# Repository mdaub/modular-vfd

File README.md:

# modular-vfd
A design for a modular vacuum fluorescent display using IV-11 VFD tubes

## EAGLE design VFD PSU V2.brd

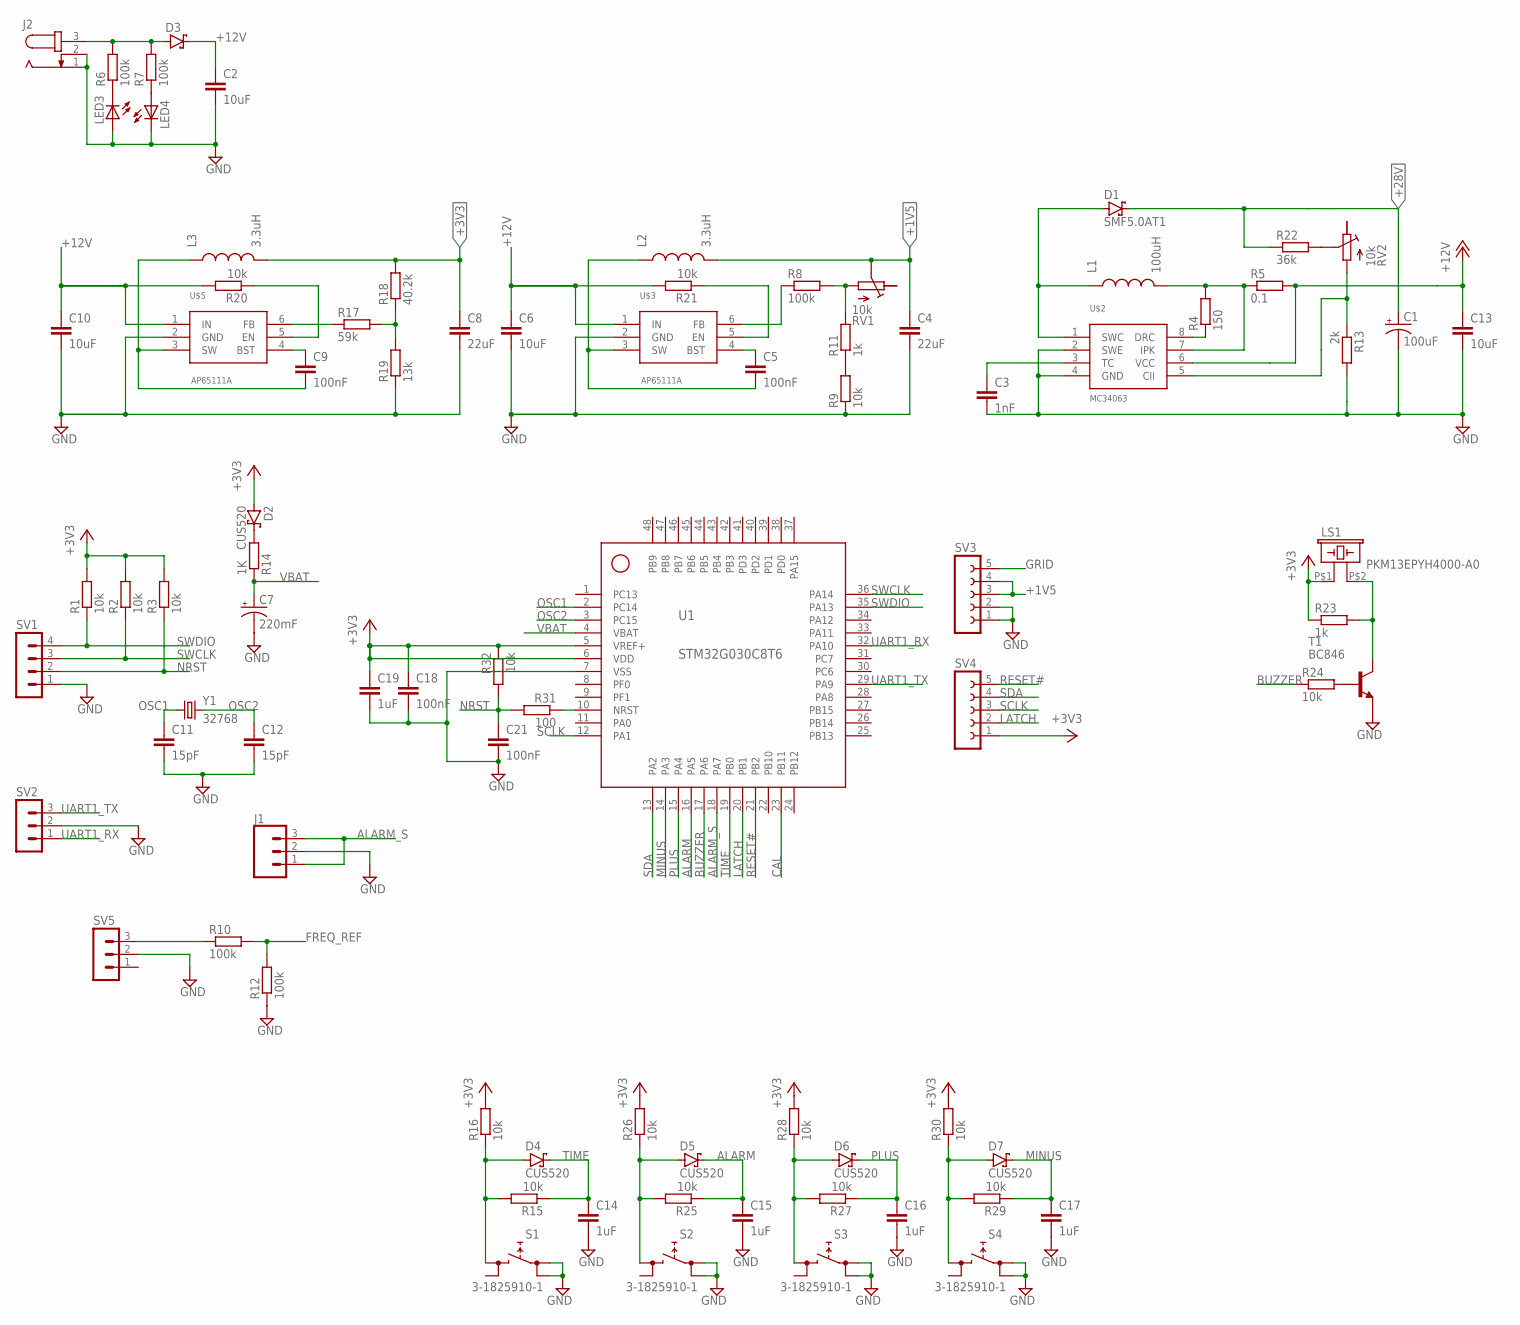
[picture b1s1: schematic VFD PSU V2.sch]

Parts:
C1: 100uF; PANASONIC_C
C2, C6, C10, C13: 10uF; C0805
C3: 1nF; C0603
C4, C8: 22uF; C0805
C5, C9, C18, C21: 100nF; C0603
C7: 220mF; 4.8-COINCELL-SCAP
C11, C12: 15pF; C0402
C14, C15, C16, C17, C19: 1uF; C0603
D1: SMF5.0AT1; SOD123FL
D2, D4, D5, D6, D7: CUS520; SOD323_ST
D3: SCHOTTKY-DIODESMD; SMB
J1: CONN_03JST-PTH-NS; JST-3-PTH-NS
J2: JACK-PLUG0; SPC4077
L1: 100uH; 2-SMD
L2, L3: 3.3uH; 1008
LED3, LED4: LEDSMT1206; 1206
LS1: PKM13EPYH4000-A0
R1, R2, R3, R9, R15, R16, R20, R21, R24, R25, R26, R27, R28, R29, R30, R32: 10k; R0603
R4: 150; R0603
R5: 0.1; R0805
R6, R7, R8, R10, R12: 100k; R0603
R11, R23: 1k; R0603
R13: 2k; R0603
R14: 1K; R0603
R17: 59k; R0603
R18: 40.2k; R0603
R19: 13k; R0603
R22: 36k; R0603
R31: 100; R0603
RV1, RV2: 10k; TC33X-2
S1, S2, S3, S4: 3-1825910-1; PANASONISWITCH
SV1: MA04-1
SV2, SV5: MA03-1
SV3, SV4: FE05W
T1: BC846; SOT23
U1: STM32G030C8T6; LQFP48
U$2: MC34063; SO08
U$3, U$5: AP65111A; TSOT23-6
Y1: 32768; 2-SMD-NO-LEAD-Q

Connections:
+1V5: C4.1, L2.P$2 (2), RV1.P$2 (S), SV3.3, SV3.4
+3V3: C8.1, C18.1, C19.1, D2.A, L3.P$2 (2), LS1.P$1 (1), R1.2, R2.2, R3.2, R16.2, R18.2, R23.1, R26.2, R28.2, R30.2, R32.1, SV4.1, U1.5 (VREF+), U1.6 (VDD)
+12V: C2.1, C6.1, C10.1, C13.1, D3.C, R5.2, R20.2, R21.2, U$2.6 (VCC), U$3.1 (IN), U$5.1 (IN)
+28V: C1.+, D1.C, R22.1
ALARM: C15.1, D5.C, R25.1, U1.16 (PA5)
ALARM_S: J1.1, J1.3, U1.18 (PA7)
BUZZER: R24.1, U1.17 (PA6)
CAL: U1.23 (PB11)
FREQ_REF: R10.2, R12.2
GND: C1.-, C2.2, C3.2, C4.2, C6.2, C7.P$2 (-), C8.2, C10.2, C11.2, C12.2, C13.2, C14.2, C15.2, C16.2, C17.2, C18.2, C19.2, C21.2, J1.2, J2.1, J2.2, LED3.A, LED4.C, R9.1, R12.1, R13.2, R19.1, S1.P$1 (0), S1.P$2 (0), S2.P$1 (0), S2.P$2 (0), S3.P$1 (0), S3.P$2 (0), S4.P$1 (0), S4.P$2 (0), SV1.1, SV2.2, SV3.1, SV3.2, SV5.2, T1.2 (E), U1.7 (VSS), U$2.2 (SWE), U$2.4 (GND), U$3.2 (GND), U$5.2 (GND)
GRID: SV3.5
LATCH: SV4.2, U1.20 (PB1)
MINUS: C17.1, D7.C, R29.1, U1.14 (PA3)
unnamed: LED3.C, R6.1
unnamed: LED4.A, R7.1
unnamed: R9.2, R11.1
unnamed: R8.1, U$3.6 (FB)
unnamed: L1.P$2 (2), R4.2, R5.1, U$2.7 (IPK)
unnamed: D3.A, J2.3, R6.2, R7.2
unnamed: R4.1, U$2.8 (DRC)
unnamed: R21.1, U$3.5 (EN)
unnamed: C5.2, L2.P$1 (1), U$3.3 (SW)
unnamed: C5.1, U$3.4 (BST)
unnamed: R8.2, R11.2, RV1.P$1 (E)
unnamed: D1.A, L1.P$1 (1), U$2.1 (SWC)
unnamed: R22.2, RV2.P$2 (S)
unnamed: C3.1, U$2.3 (TC)
unnamed: R10.1, SV5.3
unnamed: R20.1, U$5.5 (EN)
unnamed: C9.2, L3.P$1 (1), U$5.3 (SW)
unnamed: C9.1, U$5.4 (BST)
unnamed: D4.A, R15.2, R16.1, S1.P$3 (1)
unnamed: R17.1, U$5.6 (FB)
unnamed: R17.2, R18.1, R19.2
unnamed: R13.1, RV2.P$1 (E), U$2.5 (CII)
unnamed: D2.C, R14.2
unnamed: LS1.P$2 (2), R23.2, T1.3 (C)
unnamed: R24.2, T1.1 (B)
unnamed: D5.A, R25.2, R26.1, S2.P$3 (1)
unnamed: R31.1, U1.10 (NRST)
unnamed: D6.A, R27.2, R28.1, S3.P$3 (1)
unnamed: D7.A, R29.2, R30.1, S4.P$3 (1)
NRST: C21.1, R3.1, R31.2, R32.2, SV1.2
OSC1: C11.1, U1.2 (PC14), Y1.P$1 (1)
OSC2: C12.1, U1.3 (PC15), Y1.P$2 (2)
PLUS: C16.1, D6.C, R27.1, U1.15 (PA4)
RESET#: SV4.5, U1.21 (PB2)
SCLK: SV4.3, U1.12 (PA1)
SDA: SV4.4, U1.13 (PA2)
SWCLK: R2.1, SV1.3, U1.36 (PA14)
SWDIO: R1.1, SV1.4, U1.35 (PA13)
TIME: C14.1, D4.C, R15.1, U1.19 (PB0)
UART1_RX: SV2.1, U1.32 (PA10)
UART1_TX: SV2.3, U1.29 (PA9)
VBAT: C7.P$1 (+), R14.1, U1.4 (VBAT)

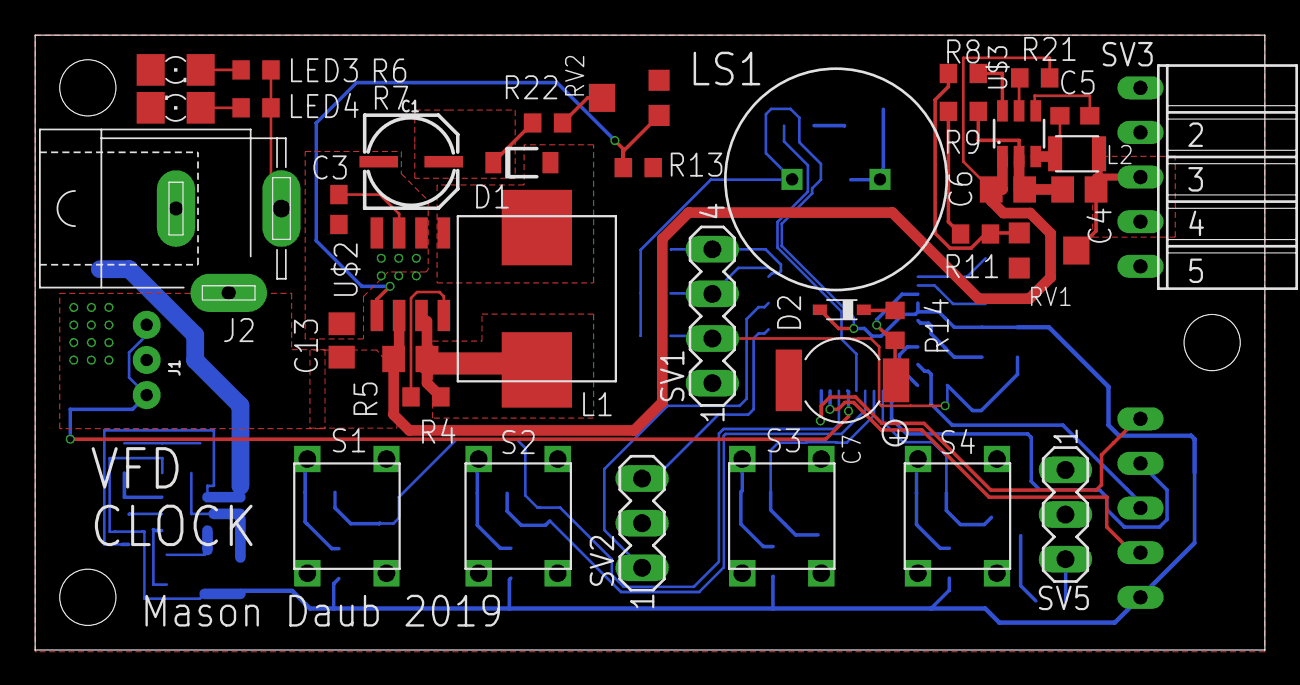
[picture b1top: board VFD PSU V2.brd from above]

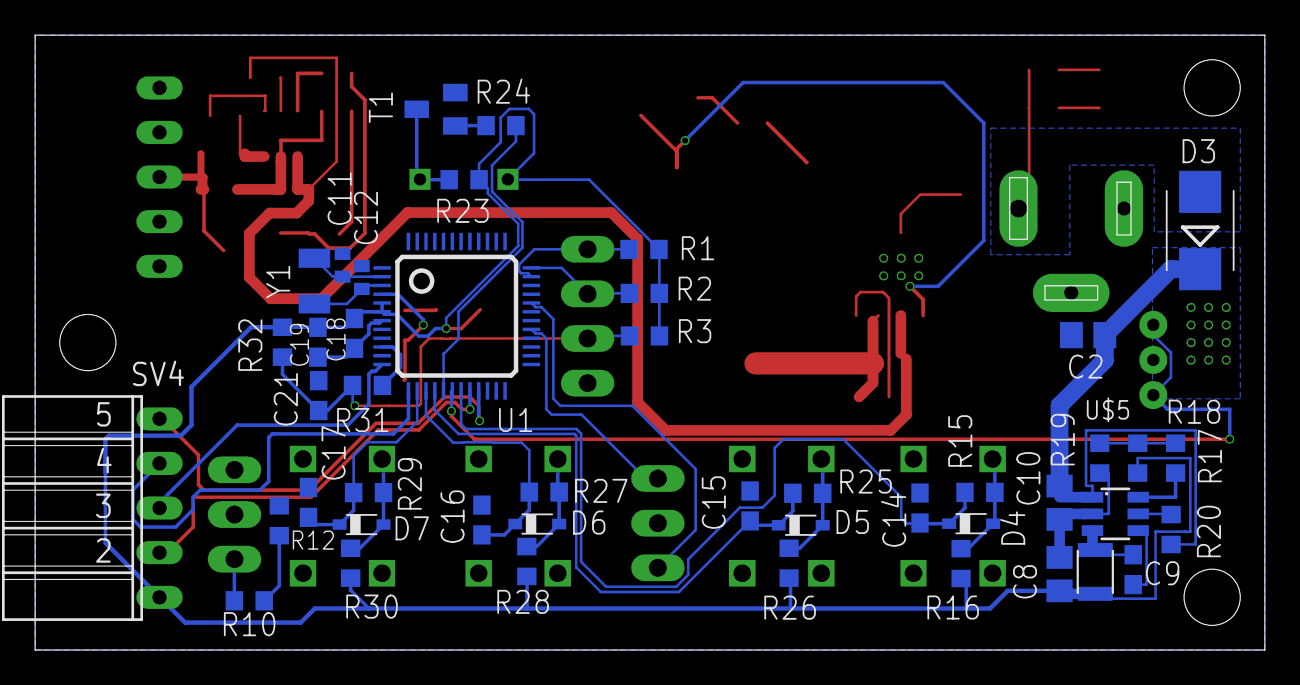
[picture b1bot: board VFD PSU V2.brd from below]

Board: 2 copper layers, 70.0 x 35.0 mm, 84 parts (45 on the bottom side), 53 nets.

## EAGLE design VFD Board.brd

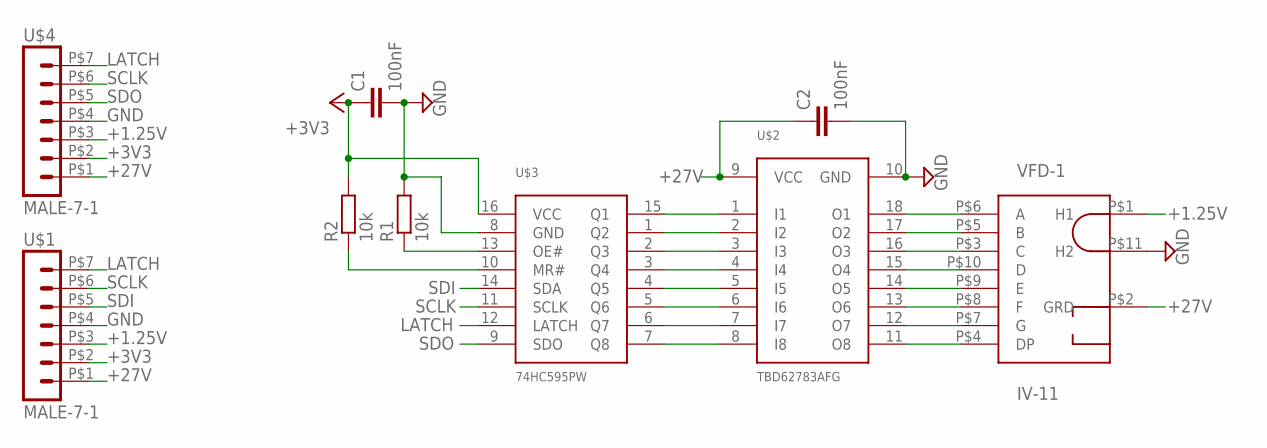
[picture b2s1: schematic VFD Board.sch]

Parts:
C1, C2: 100nF; C0603
R1, R2: 10k; R0603
U$1, U$4: MALE-7-1; 7-PIN-HEADER
U$2: TBD62783AFG; SOIC18L
U$3: 74HC595PW; TSSOP16
VFD-1: IV-11

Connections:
+1.25V: U$1.P$3 (3), U$4.P$3 (3), VFD-1.P$1 (H1)
+3V3: C1.1, R2.2, U$1.P$2 (2), U$3.16 (VCC), U$4.P$2 (2)
+27V: C2.1, U$1.P$1 (1), U$2.9 (VCC), U$4.P$1 (1), VFD-1.P$2 (GRD)
GND: C1.2, C2.2, R1.2, U$1.P$4 (4), U$2.10 (GND), U$3.8 (GND), U$4.P$4 (4), VFD-1.P$11 (H2)
LATCH: U$1.P$7 (7), U$3.12 (LATCH), U$4.P$7 (7)
unnamed: U$2.1 (I1), U$3.15 (Q1)
unnamed: U$2.2 (I2), U$3.1 (Q2)
unnamed: U$2.3 (I3), U$3.2 (Q3)
unnamed: U$2.4 (I4), U$3.3 (Q4)
unnamed: U$2.5 (I5), U$3.4 (Q5)
unnamed: U$2.6 (I6), U$3.5 (Q6)
unnamed: U$2.7 (I7), U$3.6 (Q7)
unnamed: U$2.8 (I8), U$3.7 (Q8)
unnamed: U$2.18 (O1), VFD-1.P$6 (A)
unnamed: U$2.17 (O2), VFD-1.P$5 (B)
unnamed: U$2.16 (O3), VFD-1.P$3 (C)
unnamed: U$2.15 (O4), VFD-1.P$10 (D)
unnamed: U$2.14 (O5), VFD-1.P$9 (E)
unnamed: U$2.13 (O6), VFD-1.P$8 (F)
unnamed: U$2.12 (O7), VFD-1.P$7 (G)
unnamed: U$2.11 (O8), VFD-1.P$4 (DP)
unnamed: R1.1, U$3.13 (OE#)
unnamed: R2.1, U$3.10 (MR#)
SCLK: U$1.P$6 (6), U$3.11 (SCLK), U$4.P$6 (6)
SDI: U$1.P$5 (5), U$3.14 (SDA)
SDO: U$3.9 (SDO), U$4.P$5 (5)

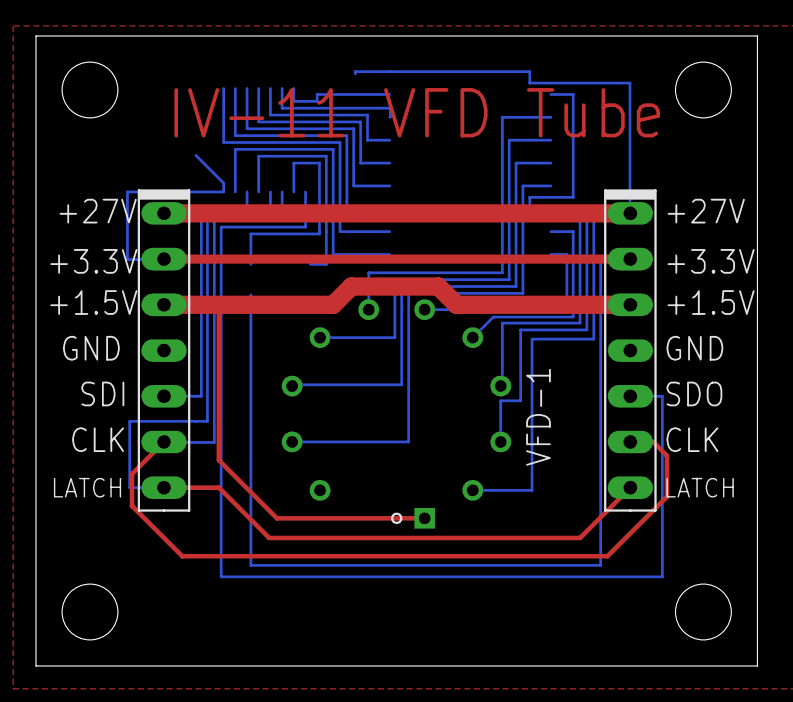
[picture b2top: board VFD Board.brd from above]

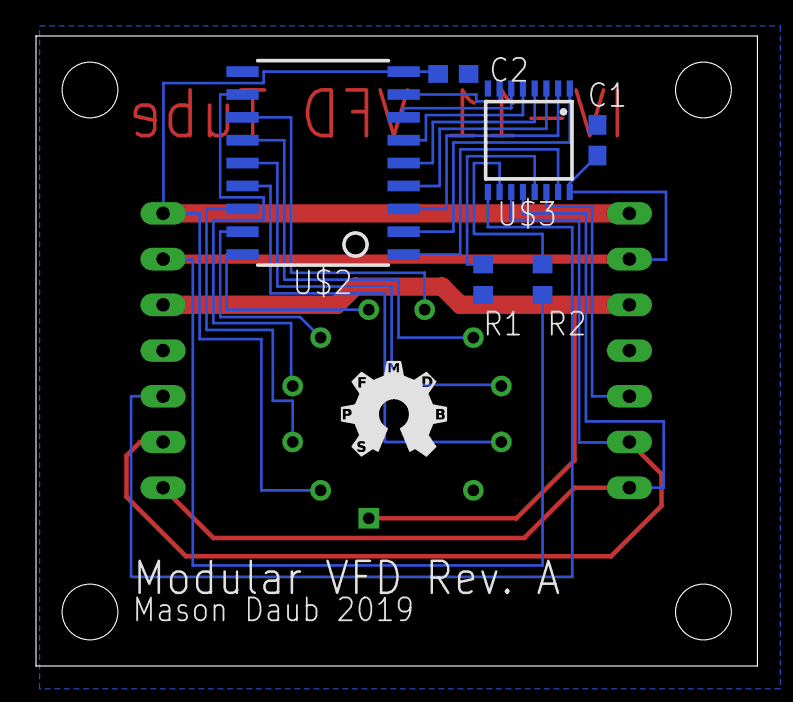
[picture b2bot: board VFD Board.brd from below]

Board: 2 copper layers, 40.1 x 35.0 mm, 9 parts (6 on the bottom side), 26 nets.

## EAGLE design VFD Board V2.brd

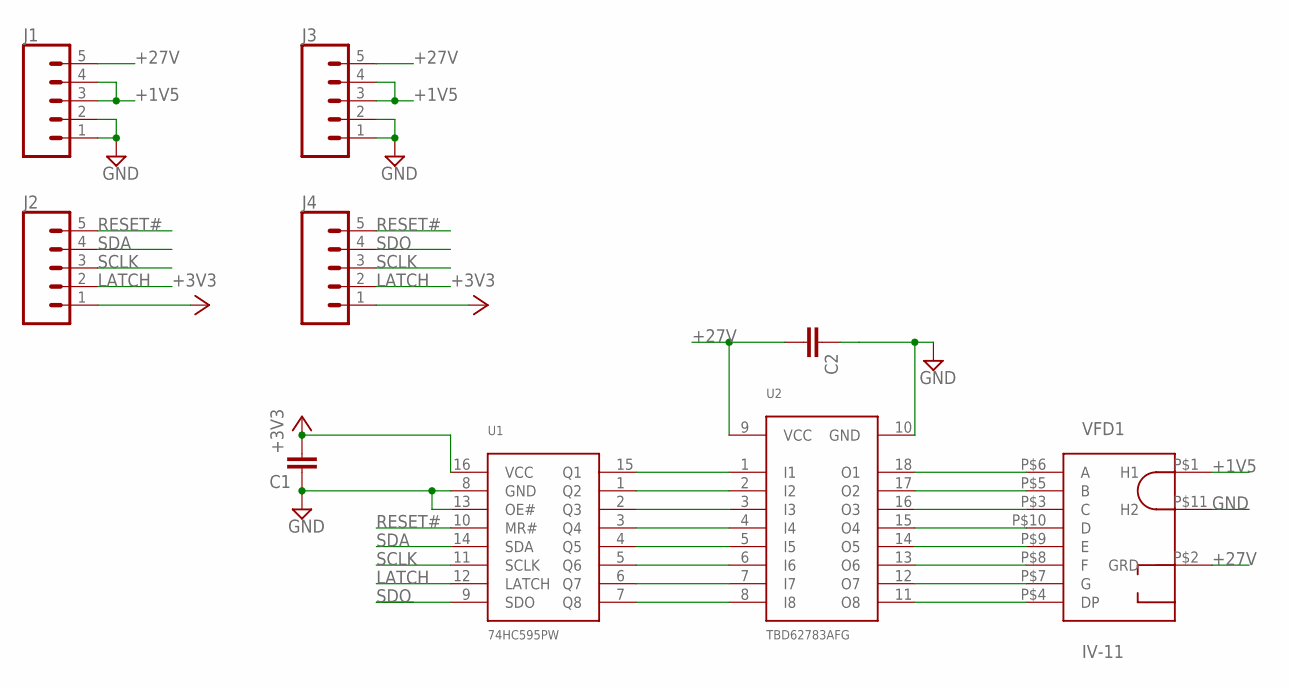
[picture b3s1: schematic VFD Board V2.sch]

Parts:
C1, C2: C-EUC0603; C0603
J1, J2, J3, J4: CONN_05NO_SILK; 1X05_NO_SILK
U1: 74HC595PW; TSSOP16
U2: TBD62783AFG; SOIC18L
VFD1: IV-11

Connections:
+1V5: J1.3, J1.4, J3.3, J3.4, VFD1.P$1 (H1)
+3V3: C1.2, J2.1, J4.1, U1.16 (VCC)
+27V: C2.2, J1.5, J3.5, U2.9 (VCC), VFD1.P$2 (GRD)
GND: C1.1, C2.1, J1.1, J1.2, J3.1, J3.2, U1.8 (GND), U1.13 (OE#), U2.10 (GND), VFD1.P$11 (H2)
LATCH: J2.2, J4.2, U1.12 (LATCH)
unnamed: U2.18 (O1), VFD1.P$6 (A)
unnamed: U1.7 (Q8), U2.8 (I8)
unnamed: U1.6 (Q7), U2.7 (I7)
unnamed: U1.5 (Q6), U2.6 (I6)
unnamed: U1.4 (Q5), U2.5 (I5)
unnamed: U1.3 (Q4), U2.4 (I4)
unnamed: U1.2 (Q3), U2.3 (I3)
unnamed: U1.1 (Q2), U2.2 (I2)
unnamed: U1.15 (Q1), U2.1 (I1)
unnamed: U2.17 (O2), VFD1.P$5 (B)
unnamed: U2.16 (O3), VFD1.P$3 (C)
unnamed: U2.15 (O4), VFD1.P$10 (D)
unnamed: U2.14 (O5), VFD1.P$9 (E)
unnamed: U2.13 (O6), VFD1.P$8 (F)
unnamed: U2.12 (O7), VFD1.P$7 (G)
unnamed: U2.11 (O8), VFD1.P$4 (DP)
RESET#: J2.5, J4.5, U1.10 (MR#)
SCLK: J2.3, J4.3, U1.11 (SCLK)
SDA: J2.4, U1.14 (SDA)
SDO: J4.4, U1.9 (SDO)

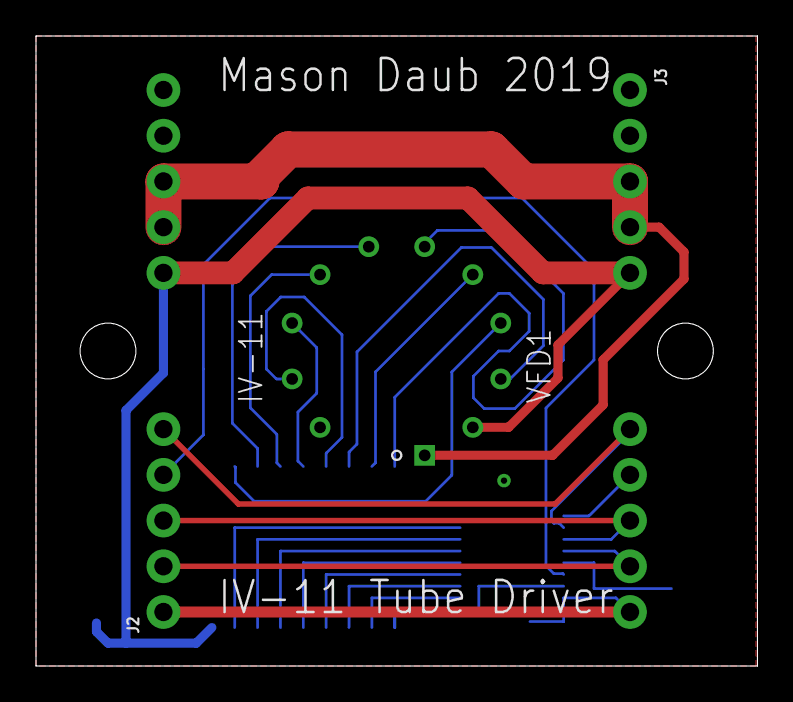
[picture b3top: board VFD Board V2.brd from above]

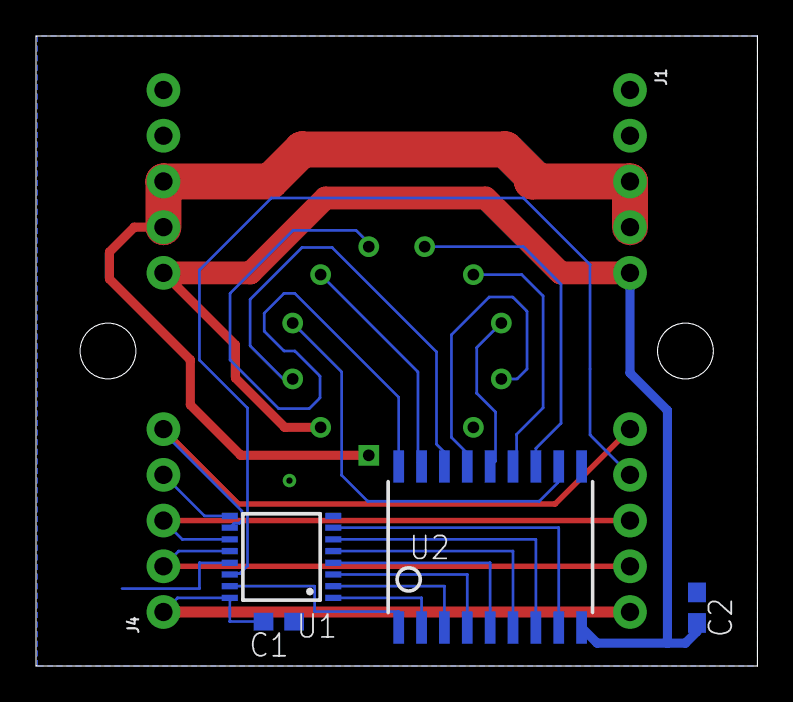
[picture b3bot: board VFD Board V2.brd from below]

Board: 2 copper layers, 40.1 x 35.0 mm, 9 parts (6 on the bottom side), 25 nets.

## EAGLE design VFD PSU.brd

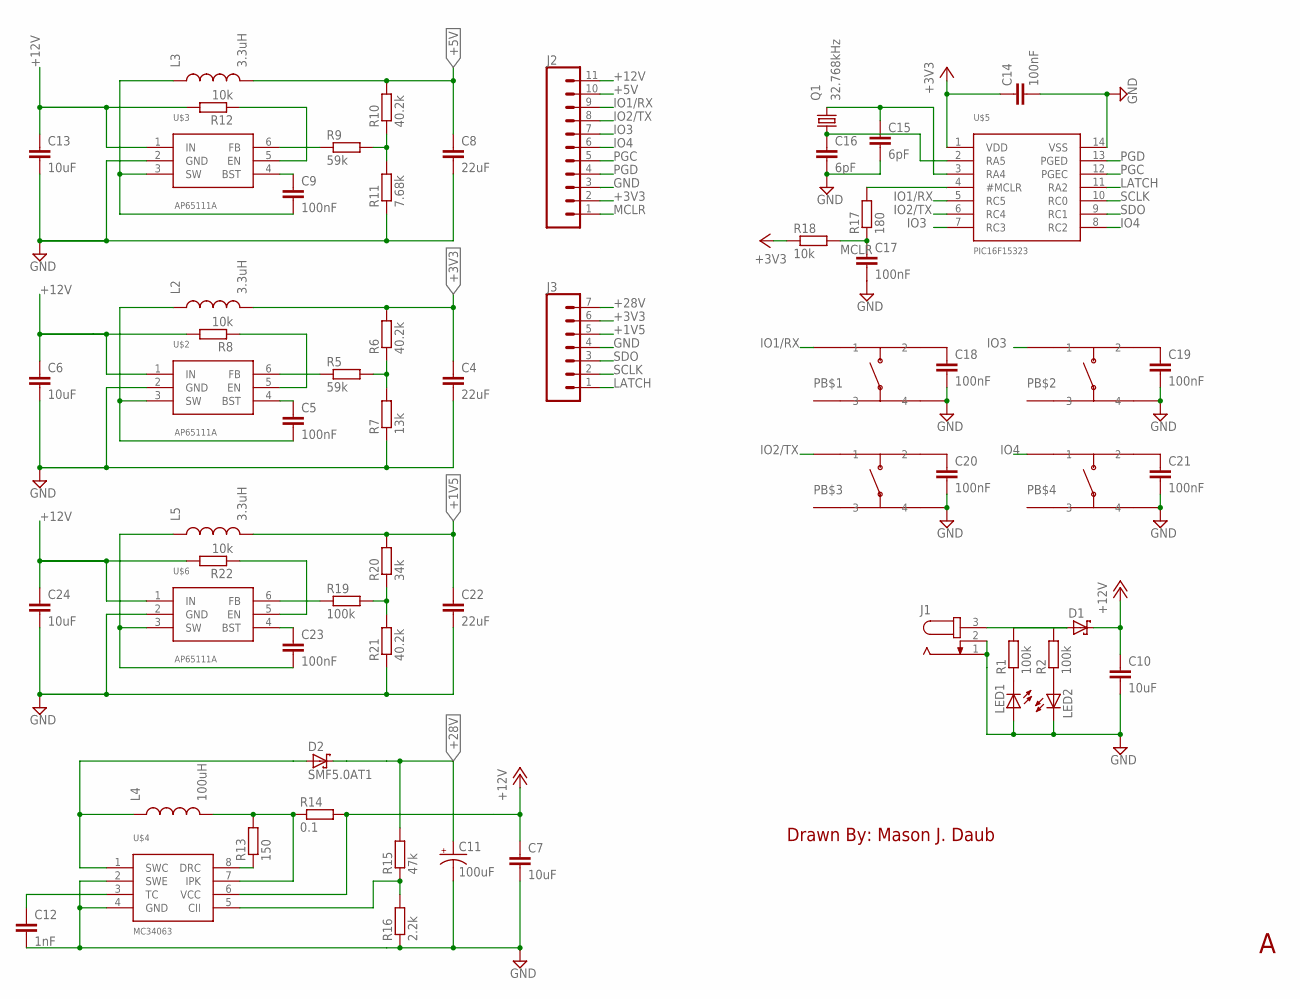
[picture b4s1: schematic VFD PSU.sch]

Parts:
C4, C8, C22: 22uF; C0805
C5, C9, C14, C17, C18, C19, C20, C21, C23: 100nF; C0603
C6, C7, C10, C13, C24: 10uF; C0805
C11: 100uF; PANASONIC_C
C12: 1nF; C0603
C15, C16: 6pF; C0603
D1: SCHOTTKY-DIODESMD; SMB
D2: SMF5.0AT1; SOD123FL
J1: JACK-PLUG0; SPC4077
J2: CONN_111X11_NO_SILK; 1X11_NO_SILK
J3: CONN_07LONGPADS; 1X07_LONGPADS
L2, L3, L5: 3.3uH; 1008
L4: 100uH; 2-SMD
LED1, LED2: LEDSMT1206; 1206
PB$1, PB$2, PB$3, PB$4: PTS645SM43SMTR92-LFS; SMDTACTILE
Q1: 32.768kHz; 8.2X3.8
R1, R2, R19: 100k; R0603
R5, R9: 59k; R0603
R6, R10, R21: 40.2k; R0603
R7: 13k; R0603
R8, R12, R18, R22: 10k; R0603
R11: 7.68k; R0603
R13: 150; R0603
R14: 0.1; R0805
R15: 47k; R0603
R16: 2.2k; R0603
R17: 180; R0603
R20: 34k; R0603
U$2, U$3, U$6: AP65111A; TSOT23-6
U$4: MC34063; SO08
U$5: PIC16F15323; SO14

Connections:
+1V5: C22.1, J3.5, L5.P$2 (2), R20.2
+3V3: C4.1, C14.1, J2.2, J3.6, L2.P$2 (2), R6.2, R18.1, U$5.1 (VDD)
+5V: C8.1, J2.10, L3.P$2 (2), R10.2
+12V: C6.1, C7.1, C10.1, C13.1, C24.1, D1.C, J2.11, R8.2, R12.2, R14.2, R22.2, U$2.1 (IN), U$3.1 (IN), U$4.6 (VCC), U$6.1 (IN)
+28V: C11.+, D2.C, J3.7, R15.2
GND: C4.2, C6.2, C7.2, C8.2, C10.2, C11.-, C12.2, C13.2, C14.2, C15.2, C16.2, C17.2, C18.2, C19.2, C20.2, C21.2, C22.2, C24.2, J1.1, J1.2, J2.3, J3.4, LED1.A, LED2.C, PB$1.P$4 (4), PB$2.P$4 (4), PB$3.P$4 (4), PB$4.P$4 (4), R7.1, R11.1, R16.1, R21.1, U$2.2 (GND), U$3.2 (GND), U$4.2 (SWE), U$4.4 (GND), U$5.14 (VSS), U$6.2 (GND)
IO1/RX: J2.9, PB$1.P$1 (1), U$5.5 (RC5)
IO2/TX: J2.8, PB$3.P$1 (1), U$5.6 (RC4)
IO3: J2.7, PB$2.P$1 (1), U$5.7 (RC3)
IO4: J2.6, PB$4.P$1 (1), U$5.8 (RC2)
LATCH: J3.1, U$5.11 (RA2)
MCLR: C17.1, J2.1, R17.1, R18.2
unnamed: R15.1, R16.2, U$4.5 (CII)
unnamed: D1.A, J1.3, R1.2, R2.2
unnamed: LED2.A, R2.1
unnamed: L4.P$2 (2), R13.2, R14.1, U$4.7 (IPK)
unnamed: LED1.C, R1.1
unnamed: R8.1, U$2.5 (EN)
unnamed: C5.2, L2.P$1 (1), U$2.3 (SW)
unnamed: C5.1, U$2.4 (BST)
unnamed: R5.1, U$2.6 (FB)
unnamed: R5.2, R6.1, R7.2
unnamed: R13.1, U$4.8 (DRC)
unnamed: R12.1, U$3.5 (EN)
unnamed: C9.2, L3.P$1 (1), U$3.3 (SW)
unnamed: C9.1, U$3.4 (BST)
unnamed: R9.1, U$3.6 (FB)
unnamed: R9.2, R10.1, R11.2
unnamed: D2.A, L4.P$1 (1), U$4.1 (SWC)
unnamed: C15.1, Q1.4 (2), U$5.3 (RA4)
unnamed: C16.1, Q1.1, U$5.2 (RA5)
unnamed: C12.1, U$4.3 (TC)
unnamed: R17.2, U$5.4 (#MCLR)
unnamed: C18.1, PB$1.P$2 (2)
unnamed: R22.1, U$6.5 (EN)
unnamed: C19.1, PB$2.P$2 (2)
unnamed: C23.2, L5.P$1 (1), U$6.3 (SW)
unnamed: C20.1, PB$3.P$2 (2)
unnamed: C23.1, U$6.4 (BST)
unnamed: C21.1, PB$4.P$2 (2)
unnamed: R19.1, U$6.6 (FB)
unnamed: R19.2, R20.1, R21.2
PGC: J2.5, U$5.12 (PGEC)
PGD: J2.4, U$5.13 (PGED)
SCLK: J3.2, U$5.10 (RC0)
SDO: J3.3, U$5.9 (RC1)

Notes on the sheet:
Drawn By: Mason J. Daub

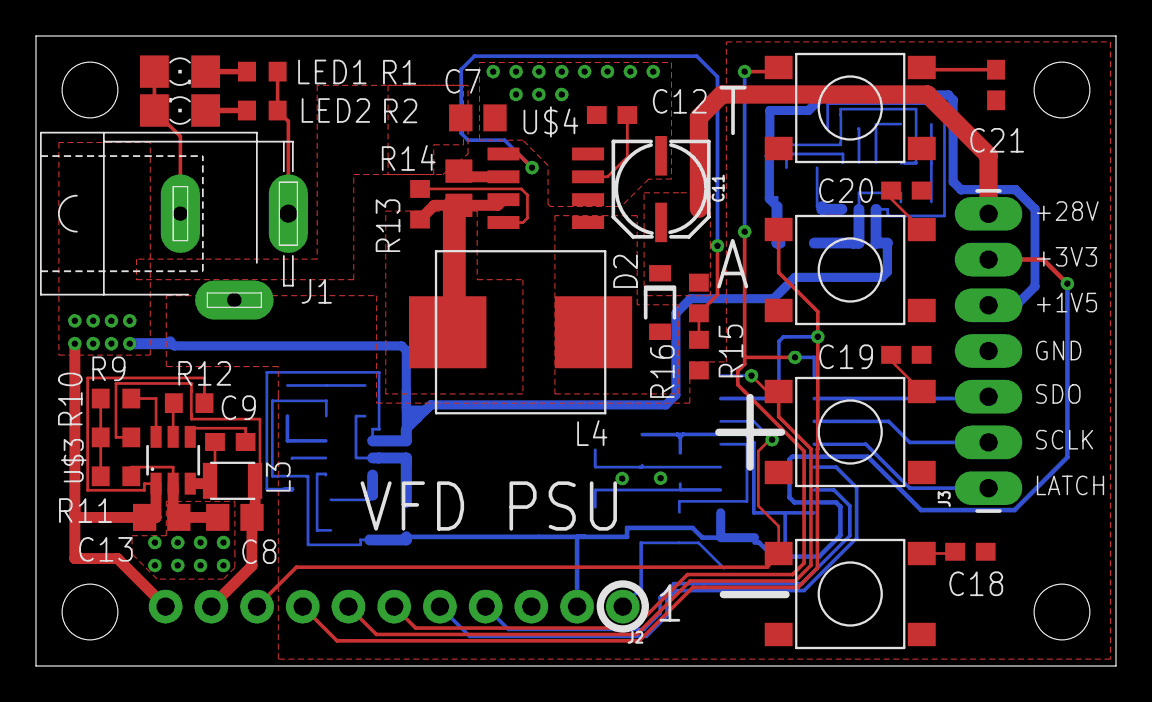
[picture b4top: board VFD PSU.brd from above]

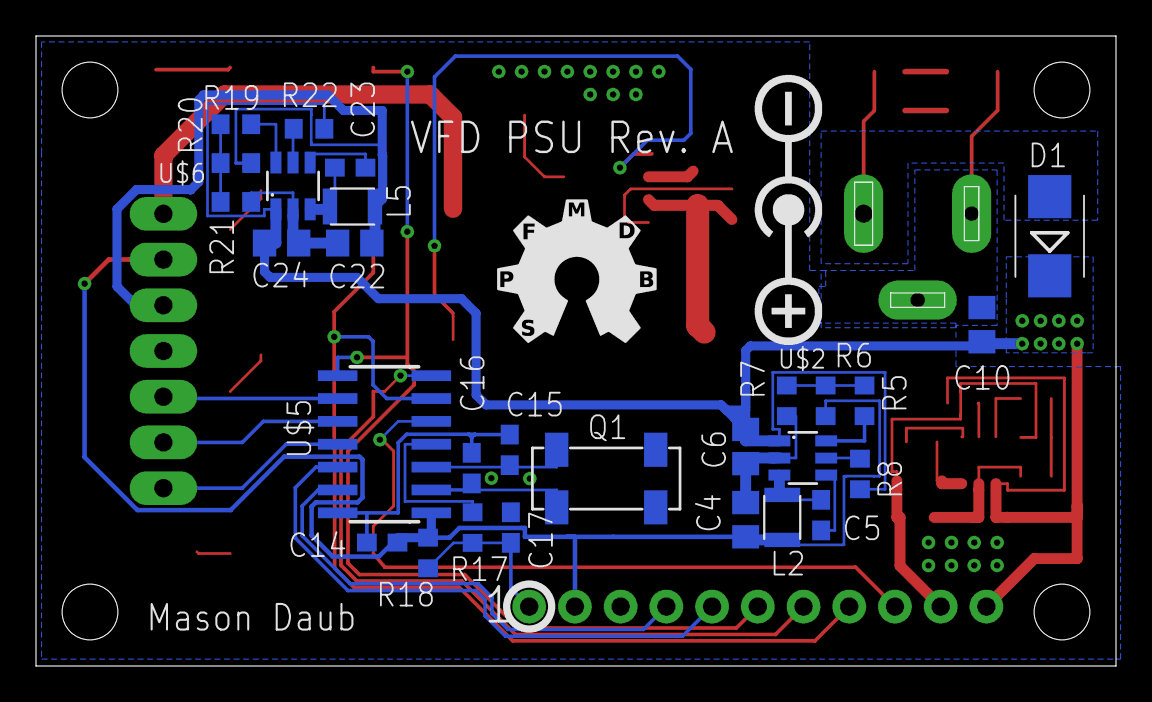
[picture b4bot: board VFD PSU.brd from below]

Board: 2 copper layers, 60.0 x 35.0 mm, 62 parts (28 on the bottom side), 46 nets.

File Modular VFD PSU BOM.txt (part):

Partlist exported from C:/Users/Mason/Documents/EAGLE/projects/Modular VFD/Modular VFD PSU.sch at 2/21/2019 3:57 AM

Qty Value                Device                         Package       Parts                                     Description                                                                                                     MF MPN OC_FARNELL OC_NEWARK PROD_ID   SPICEPREFIX VALUE
1                        CONN_07LONGPADS                1X07_LONGPADS J3                                        Multi connection point. Often used as Generic Header-pin footprint for 0.1 inch spaced/style header connections                                                        
1                        CONN_111X11_NO_SILK            1X11_NO_SILK  J2                                        Multi connection point. Often used as Generic Header-pin footprint for 0.1 inch spaced/style header connections                                                        
1                        JACK-PLUG0                     SPC4077       J1                                        DC POWER JACK                                                                                                          unknown    unknown                              
2                        LEDSMT1206                     1206          LED1, LED2                                LED                                                                                                                                                                    
1                        SCHOTTKY-DIODESMD              SMB           D1                                        Schottky Diode                                                                                                                                                         
1   0.1                  R-EU_R0805                     R0805         R14                                       RESISTOR, European symbol                                                                                                                             R                
3   100k                 R-EU_R0603                     R0603         R1, R2, R19                               RESISTOR, European symbol                                                                                                                                              
9   100nF                C-EUC0603                      C0603         C5, C9, C14, C17, C18, C19, C20, C21, C23 CAPACITOR, European symbol                                                                                                                            C                
1   100uF                22UF-POLAR-PANASONIC_C-35V-20% PANASONIC_C   C11                                       22µF polarized capacitors                                                                                                                   CAP-08618             22uF 
1   100uH                ETQ-P5M101YGK                  2-SMD         L4                                        100uH j-lead surface mount inductor manufactured by panasonic                                                                                                          
4   10k                  R-EU_R0603                     R0603         R8, R12, R18, R22                         RESISTOR, European symbol                                                                                                                                              
5   10uF                 C-EUC0805                      C0805         C6, C7, C10, C13, C24                     CAPACITOR, European symbol                                                                                                                            C                
1   13k                  R-EU_R0603                     R0603         R7                                        RESISTOR, European symbol                                                                                                                                              
1   150                  R-EU_R0603                     R0603         R13                                       RESISTOR, European symbol                                                                                                                                              
1   180                  R-EU_R0603                     R0603         R17                                       RESISTOR, European symbol                                                                                                                                              
1   1nF                  C-EUC0603                      C0603         C12                                       CAPACITOR, European symbol                                                                                                                            C                
1   2.2k                 R-EU_R0603                     R0603         R16                                       RESISTOR, European symbol                                                                                                                                              
3   22uF                 C-EUC0805                      C0805         C4, C8, C22                               CAPACITOR, European symbol                                                                                                                            C                
3   3.3uH                L1008                          1008          L2, L3, L5                                                                                                                                                                                                       
1   32.768kHz            KX-327-S                       8.2X3.8       Q1                                        Tuning Fork Crystals (kHz) SMD: watch crystal                                                                                                                                        
1   35k                  R-EU_R0603                     R0603         R20                                       RESISTOR, European symbol                                                                                                                                              
2   40.2k                R-EU_R0603                     R0603         R6, R10                                   RESISTOR, European symbol                                                                                                                                              
1   40k                  R-EU_R0603                     R0603         R21                                       RESISTOR, European symbol                                                                                                                                              
1   47k                  R-EU_R0603                     R0603         R15                                       RESISTOR, European symbol                                                                                                                                              
2   59k                  R-EU_R0603                     R0603         R5, R9                                    RESISTOR, European symbol                                                                                                                                              
2   6pF                  C-EUC0603                      C0603         C15, C16                                  CAPACITOR, European symbol                                                                                                                            C                
1   7.68k                R-EU_R0603                     R0603         R11                                       RESISTOR, European symbol                                                                                                                                              
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
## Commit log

2019-11-23 Adding existing files
2019-11-24 Optimised area, preparing for manufacturing

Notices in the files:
parts and their libraries:
SparkFun-Connectors: Licensing: Creative Commons ShareAlike 4.0 International - https://creativecommons.org/licenses/by-sa/4.0
crystal-geyer_V1_0: Copyright: Geyer-Electronic
